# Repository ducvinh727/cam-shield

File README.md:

# esp32-cam-shield

## Features

esp32-cam-demo có thể:
- Power input 5.5V to 28VDC (1.2A/5V output) and 5V USB
- detected motions ( 0-8m), take a picture and send to server.
- stream video jpeg
- QR code Scan

# Nguyên lý hoạt động

- khi radar phát hiện bất cứ chuyển động nào sẽ gửi tín hiệu đến esp32 ( được cách li quang thông qua opto) khi đó. esp32 sẽ ghi lại ảnh và gửi lên serve.

## Hardware

### Các module đi kèm

[ESP32 WIFI UNO](https://iotmaker.vn/esp32-wifi-uno.html)

[OLED SSD1306](https://iotmaker.vn/ssd1306-oled-096inch-128x64-i2c.html?combination=3_4)

[RADAR 220V AC](https://iotmaker.vn/cam-bien-vat-can-radar-220vac.html)

[MODULE CAMERA OV7725](https://iotmaker.vn/module-camera-ov7725.html)

### Schematics

### PCB Layout

### 3D

[]

### Gerber

[Download](./assets/esp32-cam-shield.zip)

### BOM 

| Designator | Package | Quantity | Designation  |
|---------------------|--------------------------------|----------|-------------------------|
| U1	                  | PIN HEADER Straight 2x10       | 1        | HEADER CAMERA       |
| U2                      | TC817		           | 1        | OPTO PC817          |
| U4                      | PIN HEADER Straight 1x4        | 1        | HEADER OLED SSD1306 | 
| D2                      | LED_0603                       | 1        | LED_Blue            |
| C1                      | CP_Elec_4x5.3                  | 1        | 10uF/15             |
| R1			  | R_0603                         | 1        | 220k                |
| R2,R3		          | R_0603                         | 1        | 10k                 |
| R4                      | R_0603                         | 1        | 4,7K                |
| J1                      | TerminalBlockPT-3.5mm_2pol     | 1        | CONNECTOR 2         |

### Remark

This project was in development phase - we will remove this remark after release

# License

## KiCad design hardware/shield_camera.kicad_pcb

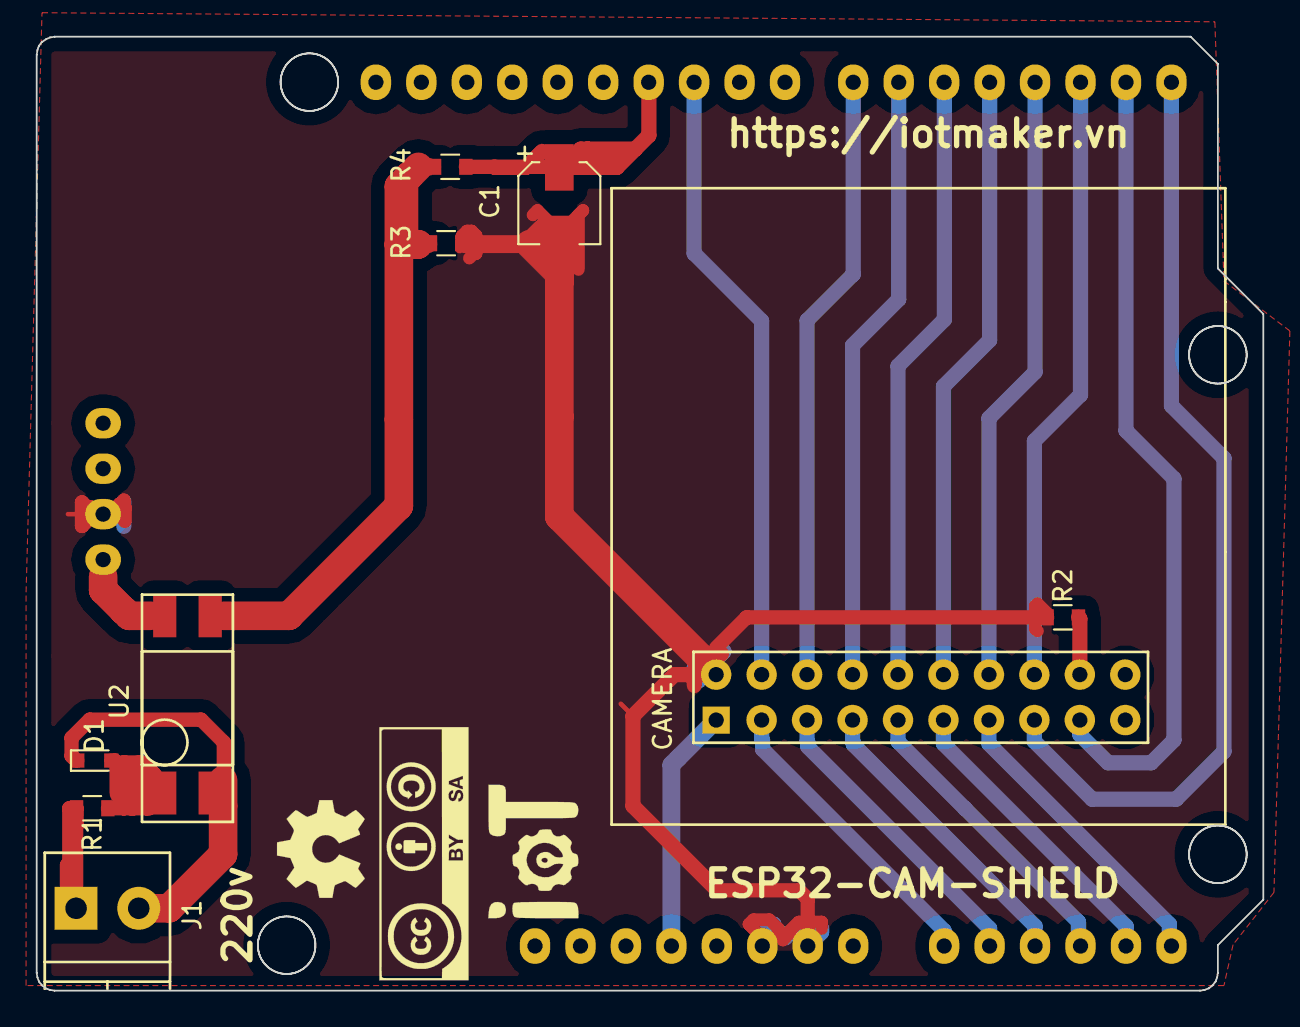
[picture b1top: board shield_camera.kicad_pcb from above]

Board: 2 copper layers, 68.5 x 53.3 mm, 10 parts (0 on the bottom side), 24 nets.

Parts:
C1: 10uF; CP_Elec_4x5.3
CAMERA: camera; ov7725
D1: LED; D_0603
J1: RADAR; TerminalBlock_Pheonix_PT-3.5mm_2pol
R1: 220K; R_0603
R2, R3: 10K; R_0603
R4: 4.7K; R_0603
S1: ESP-UNO; ESP-UNO-SH
U2: PC817; CP817

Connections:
3V3: CAMERA.1, S1.4
3V3/OLED1: S1.36, U2.4
GND: C1.2, CAMERA.18, R2.1, R3.1, S1.6, S1.7, S1.35
GPIO0: CAMERA.12, S1.18
GPIO02: CAMERA.11, S1.17
GPIO04: CAMERA.13, S1.19
GPIO05: CAMERA.17, S1.25
GPIO12: CAMERA.5, S1.12
GPIO13: CAMERA.6, S1.13
GPIO14: CAMERA.4, S1.11
GPIO15: CAMERA.7, S1.14
GPIO16: CAMERA.8, S1.15
GPIO17: CAMERA.9, S1.16
GPIO23: C1.1, R4.1, S1.26
GPIO25: CAMERA.14, S1.20
GPIO26: CAMERA.15, S1.21
GPIO27: CAMERA.16, S1.22
GPIO36: CAMERA.2, S1.9
GPIO39: CAMERA.3, S1.10
unnamed: D1.1, J1.2, U2.2
unnamed: D1.2, R1.1, U2.1
unnamed: J1.1, R1.2
unnamed: CAMERA.10, R2.2
unnamed: R3.2, R4.2, U2.3

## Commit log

2017-07-13 Fsdf
2017-07-13 sdfasf
